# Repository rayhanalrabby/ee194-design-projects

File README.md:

# EE194 — Project-Based Learning

Team design projects from EE194, Maynooth University (Semester 1, Year 1).
Each project ran ~7 weeks in a rotating group, covering research,
design, prototyping, and a written report and presentation.

| # | Project | Tools | Team |
|---|---------|-------|------|
| 01 | [3D-Printed Paperclip](01-3d-printed-paperclip/) | SolidWorks, PLA FDM printing | 7 |
| 02 | [100 W DC–AC Inverter PCB](02-100w-dc-ac-inverter-pcb/) | EAGLE, schematic capture, board layout | 6 |

My contribution is noted in each project's README. These were group
projects — teammates are credited by name in the reports.

> Design coursework. Neither project was validated for production
> use. See individual READMEs for safety notes.

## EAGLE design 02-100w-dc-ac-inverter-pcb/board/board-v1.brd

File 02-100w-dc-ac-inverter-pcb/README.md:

# 100 W DC–AC Inverter — PCB Design

Design a 100 W inverter that converts DC (battery or solar) to
mains-style AC, taken from circuit research through to a
manufacturable PCB layout in EAGLE.

## Approach
Started from published 100 W inverter topologies, then each of the
six of us built schematics in EAGLE independently — partly to get
everyone fluent in the tool, partly to have two or three viable
candidates to choose from rather than committing to the first idea.
The strongest schematic was carried through to board layout.

Seven weeks, split across research, schematic capture, layout,
report, and presentation.

## Files
- `schematic/` — EAGLE .sch files
- `board/` — EAGLE .brd layout
- `gerbers/` — fabrication output
- `docs/` — report and BOM

## Takeaways
- Schematic correctness and board manufacturability are separate
  problems. A circuit that simulates fine still has to survive
  trace-width, clearance, and thermal constraints on the copper.
- Mains-level output means clearance and isolation stop being
  cosmetic. Getting the high-voltage side laid out safely drove more
  of the layout decisions than component placement did.

---
EE194 Project-Based Learning, Maynooth University, Semester 1, Year 1 (2024).
Group of 6 — my contribution: [fill in: schematic design / layout /
component selection / report section].

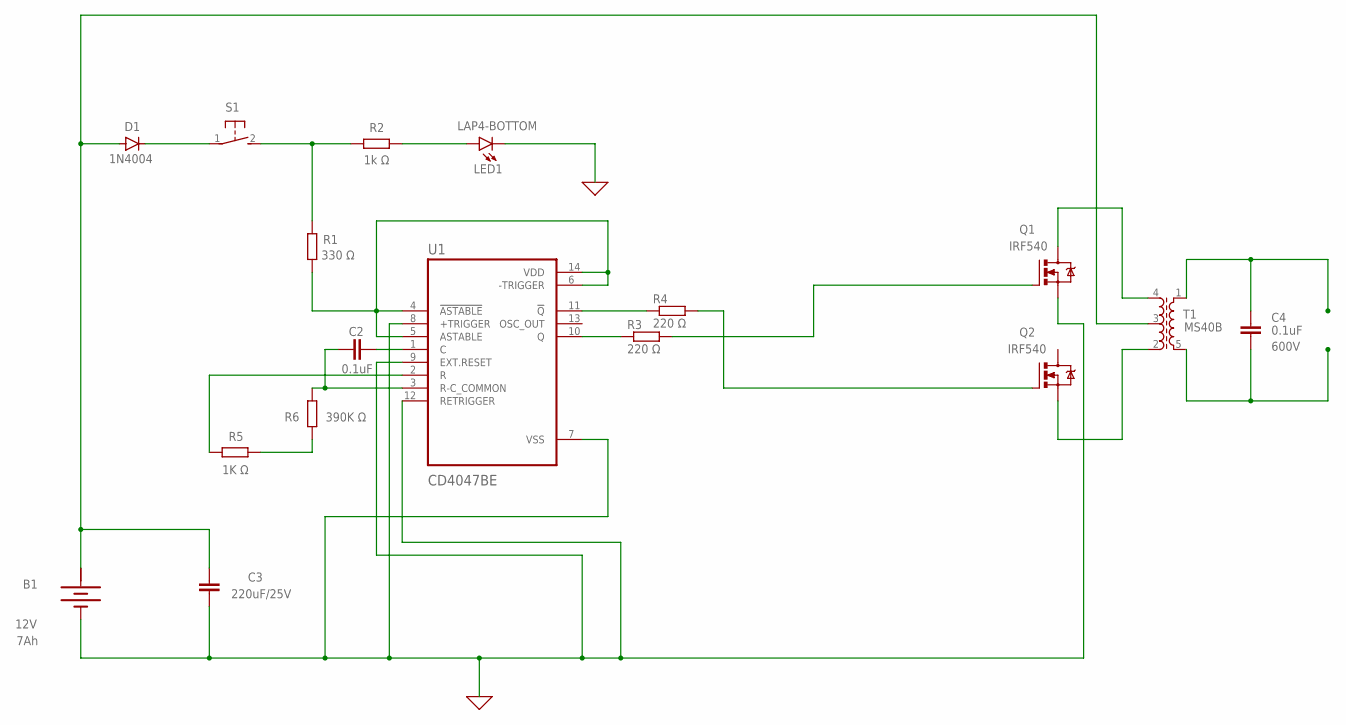
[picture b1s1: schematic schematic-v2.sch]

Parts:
B1: 12V; BATTERY
C2, C4: 0.1uF; C2.5-3
C3: 220uF/25V; C2.5-3
D1: 1N4004; DO41-10
LED1: LAP4-BOTTOM; P47F-BOTTOM
Q1, Q2: IRF540; TO220BV
R1: 330 Ω; 0204/7
R2: 1k Ω; 0204/7
R3, R4: 220 Ω; 0204/7
R5: 1K Ω; 0204/7
R6: 390K Ω; 0204/7
S1: 31-XX; B3F-31XX
T1: MS40B; MS40
U1: CD4047BE; DIP794W45P254L1969H508Q14

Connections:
0: B1.-, C3.2, LED1.C, Q1.S, U1.7 (VSS), U1.8 (+TRIGGER), U1.9 (EXT.RESET), U1.12 (RETRIGGER)
+: B1.+@1 (+)
unnamed: C2.2, U1.1 (C)
unnamed: C2.1, R6.2, U1.3 (R-C_COMMON)
unnamed: C4.1, T1.1 (5)
unnamed: C4.2, T1.5 (1)
unnamed: Q2.S, T1.2
unnamed: Q1.D, T1.4
unnamed: B1.+, C3.1, D1.A, T1.3
unnamed: R5.1, U1.2 (R)
unnamed: R1.1, U1.4 (!ASTABLE), U1.5 (ASTABLE), U1.6 (-TRIGGER), U1.14 (VDD)
unnamed: R1.2, R2.2, S1.2 (S)
unnamed: LED1.A, R2.1
unnamed: D1.C, S1.1
unnamed: Q1.G, R3.2
unnamed: Q2.G, R4.2
unnamed: R3.1, U1.10 (Q)
unnamed: R4.1, U1.11 (!Q)
unnamed: R5.2, R6.1

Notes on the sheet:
600V
7Ah

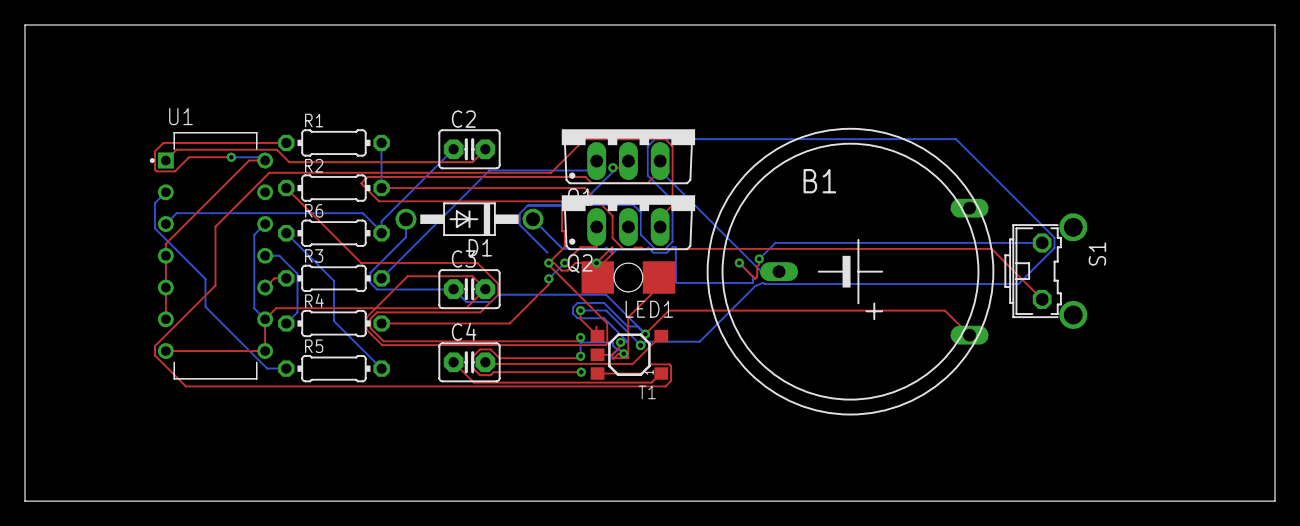
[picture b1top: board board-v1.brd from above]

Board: 2 copper layers, 100.0 x 38.1 mm, 17 parts (0 on the bottom side), 18 nets.

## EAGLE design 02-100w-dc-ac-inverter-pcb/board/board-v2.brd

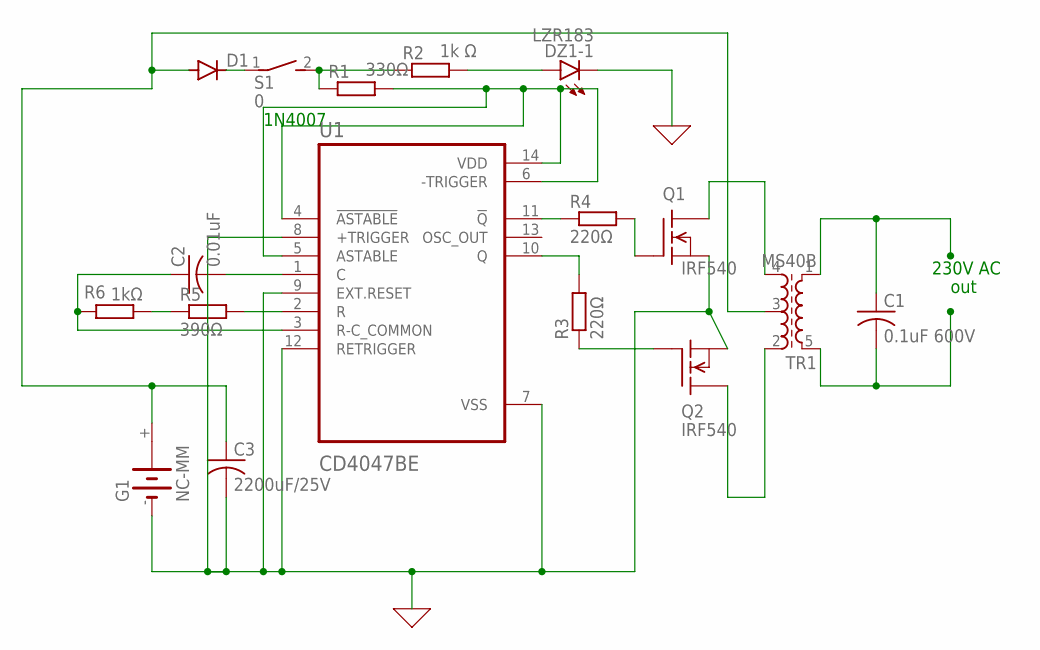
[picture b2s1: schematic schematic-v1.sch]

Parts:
C1: 0.1uF 600V; C025-024X044
C2: 0.01uF; C025-024X044
C3: 2200uF/25V; C025-024X044
D1: 1N4004; DO41-10
DZ1: LZR183
G1: NC-MM
Q1, Q2: IRF540; TO220
R1: 330Ω; 0207/7
R2: 1k Ω; 0207/7
R3, R4: 220Ω; 0207/7
R5: 390Ω; 0207/7
R6: 1kΩ; 0207/7
S1: 0; DS-01
TR1: MS40B; MS40
U1: CD4047BE; DIP794W45P254L1969H508Q14

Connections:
0: C3.2, DZ1.K1 (C), G1.-, Q1.3 (S), Q2.3 (S), U1.7 (VSS), U1.8 (+TRIGGER), U1.9 (EXT.RESET), U1.12 (RETRIGGER)
unnamed: C2.2, U1.1 (C)
unnamed: R3.2, U1.10 (Q)
unnamed: Q2.1 (G), R3.1
unnamed: C3.1, D1.A, G1.+, TR1.3
unnamed: Q2.2 (D), TR1.2
unnamed: Q1.2 (D), TR1.4
unnamed: C1.2, TR1.5 (1)
unnamed: C1.1, TR1.1 (5)
unnamed: R1.1, R2.1, S1.2
unnamed: R1.2, U1.4 (!ASTABLE), U1.5 (ASTABLE), U1.6 (-TRIGGER), U1.14 (VDD)
unnamed: DZ1.A1 (A), R2.2
unnamed: R5.2, U1.2 (R)
unnamed: C2.1, R6.2, U1.3 (R-C_COMMON)
unnamed: R5.1, R6.1
unnamed: R4.1, U1.11 (!Q)
unnamed: Q1.1 (G), R4.2
unnamed: D1.C, S1.1

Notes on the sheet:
1N4007
230V AC
out

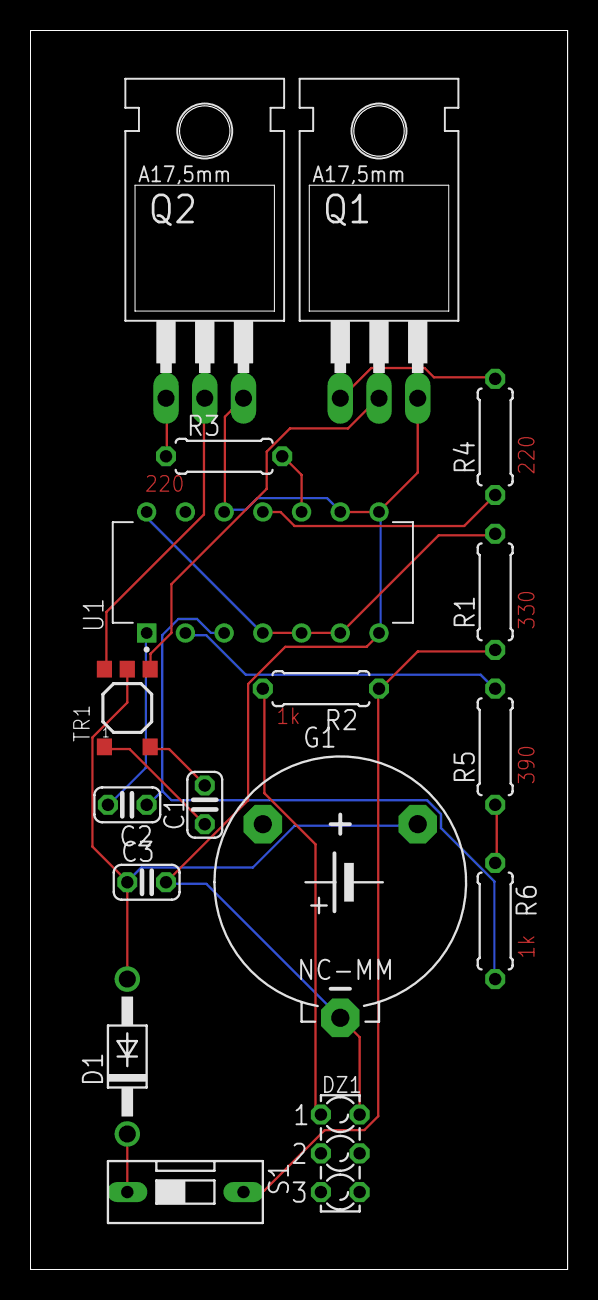
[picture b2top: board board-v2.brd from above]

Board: 2 copper layers, 35.2 x 81.3 mm, 17 parts (0 on the bottom side), 18 nets.
